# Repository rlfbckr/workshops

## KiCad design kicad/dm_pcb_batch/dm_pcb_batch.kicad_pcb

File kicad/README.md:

# Designing PCBs for artists and designers with KiCAD

This is an introduction to KiCAD spanning two evenings. Together, we will design a basic microcontroller board around an ATtiny microcontroller. The workshop will cover all the steps involved, from creating the schematic and designing the board to preparing it for fabrication.

## Reqiements
- You have a strong grasp of electronics and have already completed several Arduino/microcontroller projects. You are also familiar with reading schematics and understanding Ohm's law.

## Prepare for Workshop
- download KiCAD (version 9) from https://www.kicad.org/

## Additonal Resources
- [Introduction](https://docs.google.com/presentation/d/1FQOJmnPphsIvtIlYlx94JYpmJ64v6YoRFoZGHLRAc9c/edit?slide=id.p#slide=id.p) 
- [6 Horribly Common PCB Design Mistakes](https://www.youtube.com/watch?v=Z9nycymUd-I)
- [PCB Batch Miro Boards](https://miro.com/app/board/uXjVJfeq8kw=/)

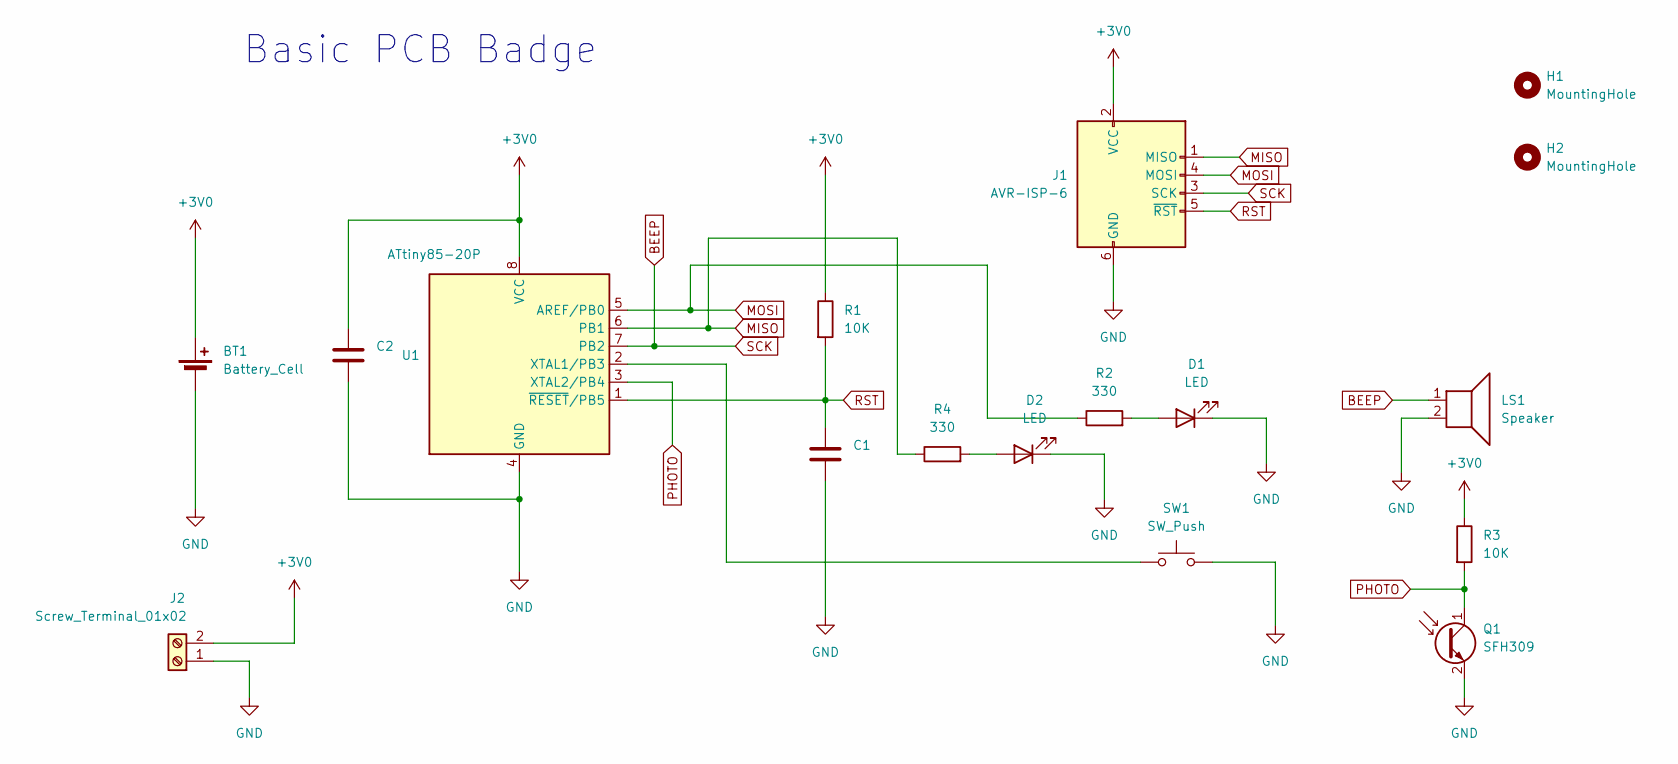
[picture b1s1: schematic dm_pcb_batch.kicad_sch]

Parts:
BT1: Battery_Cell; BatteryHolder_Multicomp_BC-2001_1x2032
C1, C2: 100n; C_Disc_D3.8mm_W2.6mm_P2.50mm
D1, D2: LED; LED_D3.0mm
H1, H2: MountingHole; MountingHole_3.2mm_M3
J1: AVR-ISP-6; PinHeader_2x03_P2.54mm_Vertical
J2: Screw_Terminal_01x02
LS1: Speaker; Buzzer_12x9.5RM7.6
Q1: SFH309; LED_D3.0mm_Clear
R1, R3: 10K; R_Axial_DIN0207_L6.3mm_D2.5mm_P10.16mm_Horizontal
R2, R4: 330; R_Axial_DIN0207_L6.3mm_D2.5mm_P10.16mm_Horizontal
SW1: SW_Push; SW_PUSH_6mm
U1: ATtiny85-20P; DIP-8_W7.62mm

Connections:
+3V0: BT1.1 (+), C2.1, J1.2 (VCC), J2.2, R1.1, R3.1, U1.8 (VCC)
BEEP: J1.3 (SCK), LS1.1, U1.7 (PB2)
GND: BT1.2 (-), C1.2, C2.2, D1.1 (K), D2.1 (K), J1.6 (GND), J2.1, LS1.2, Q1.2 (E), SW1.2, U1.4 (GND)
MISO: J1.1 (MISO), R4.1, U1.6 (PB1)
MOSI: J1.4 (MOSI), R2.1, U1.5 (AREF/PB0)
unnamed: D1.2 (A), R2.2
unnamed: D2.2 (A), R4.2
unnamed: SW1.1, U1.2 (XTAL1/PB3)
PHOTO: Q1.1 (C), R3.2, U1.3 (XTAL2/PB4)
RST: C1.1, J1.5 (~RST), R1.2, U1.1 (~RESET/PB5)

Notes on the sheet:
Basic PCB Badge

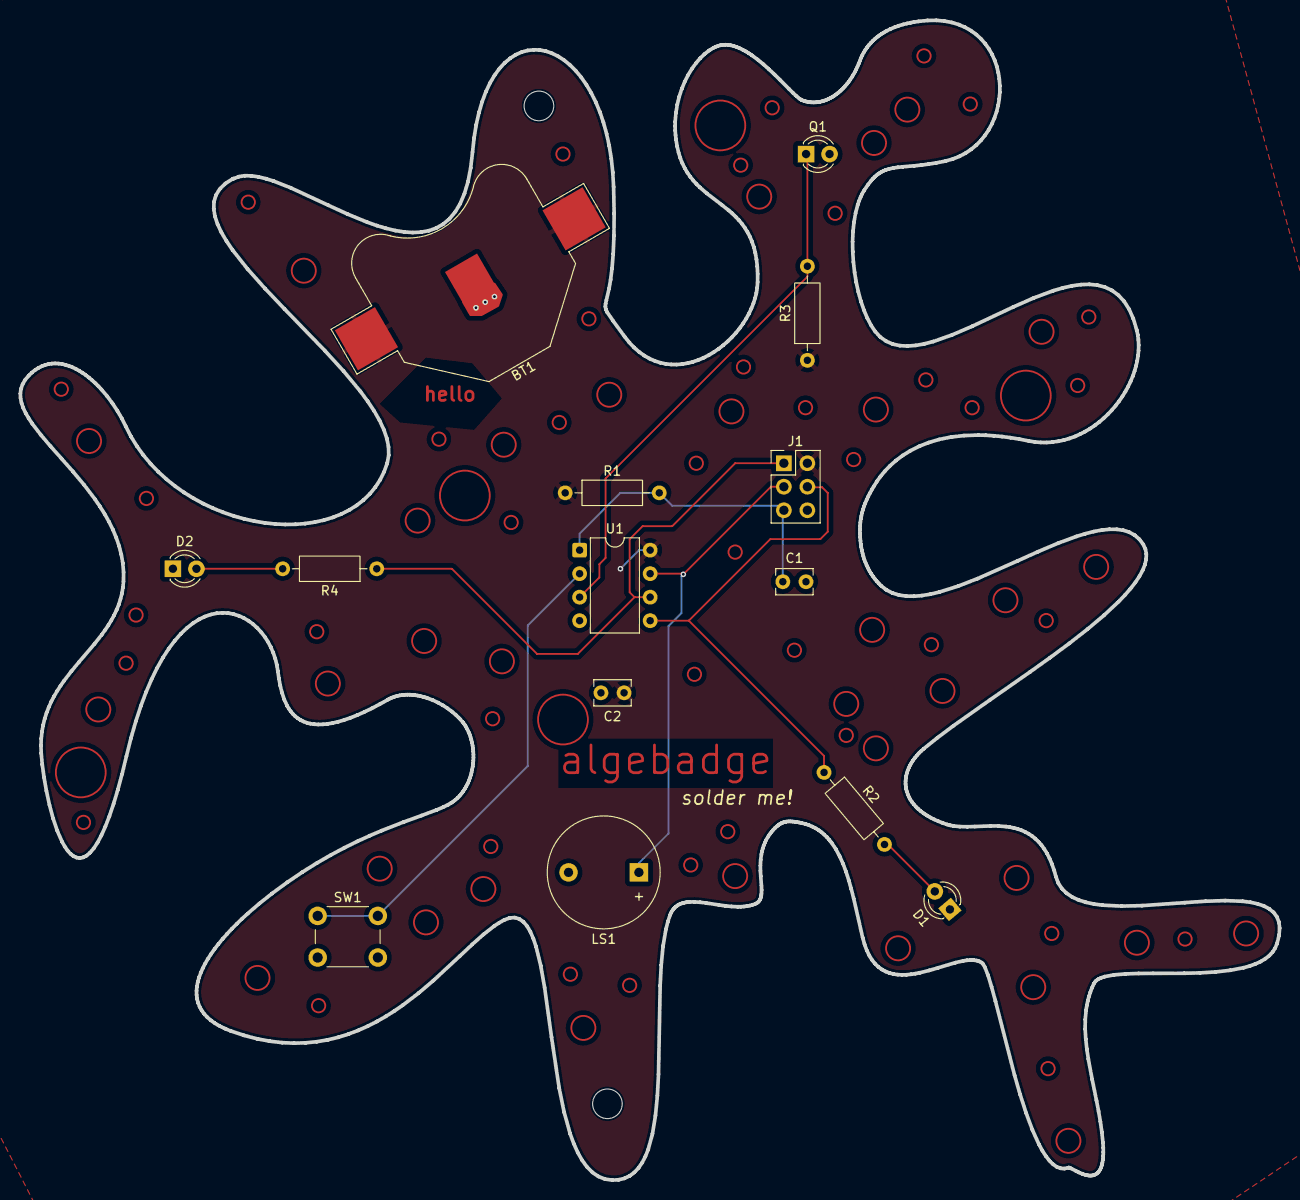
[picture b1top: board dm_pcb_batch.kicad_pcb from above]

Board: 2 copper layers, 136.0 x 125.3 mm, 16 parts (0 on the bottom side), 10 nets.

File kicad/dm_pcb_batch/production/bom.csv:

Designator,Footprint,Quantity,Value,LCSC Part #
BT1,BatteryHolder_Multicomp_BC-2001_1x2032,1,Battery_Cell,
"C1, C2",C_Disc_D3.8mm_W2.6mm_P2.50mm,2,100n,
"D1, D2",LED_D3.0mm,2,LED,
J1,PinHeader_2x03_P2.54mm_Vertical,1,AVR-ISP-6,
LS1,Buzzer_12x9.5RM7.6,1,Speaker,
Q1,LED_D3.0mm_Clear,1,SFH309,
"R1, R3",R_Axial_DIN0207_L6.3mm_D2.5mm_P10.16mm_Horizontal,2,10K,
"R2, R4",R_Axial_DIN0207_L6.3mm_D2.5mm_P10.16mm_Horizontal,2,330,
SW1,SW_PUSH_6mm,1,SW_Push,
U1,DIP-8_W7.62mm,1,ATtiny85-20P,

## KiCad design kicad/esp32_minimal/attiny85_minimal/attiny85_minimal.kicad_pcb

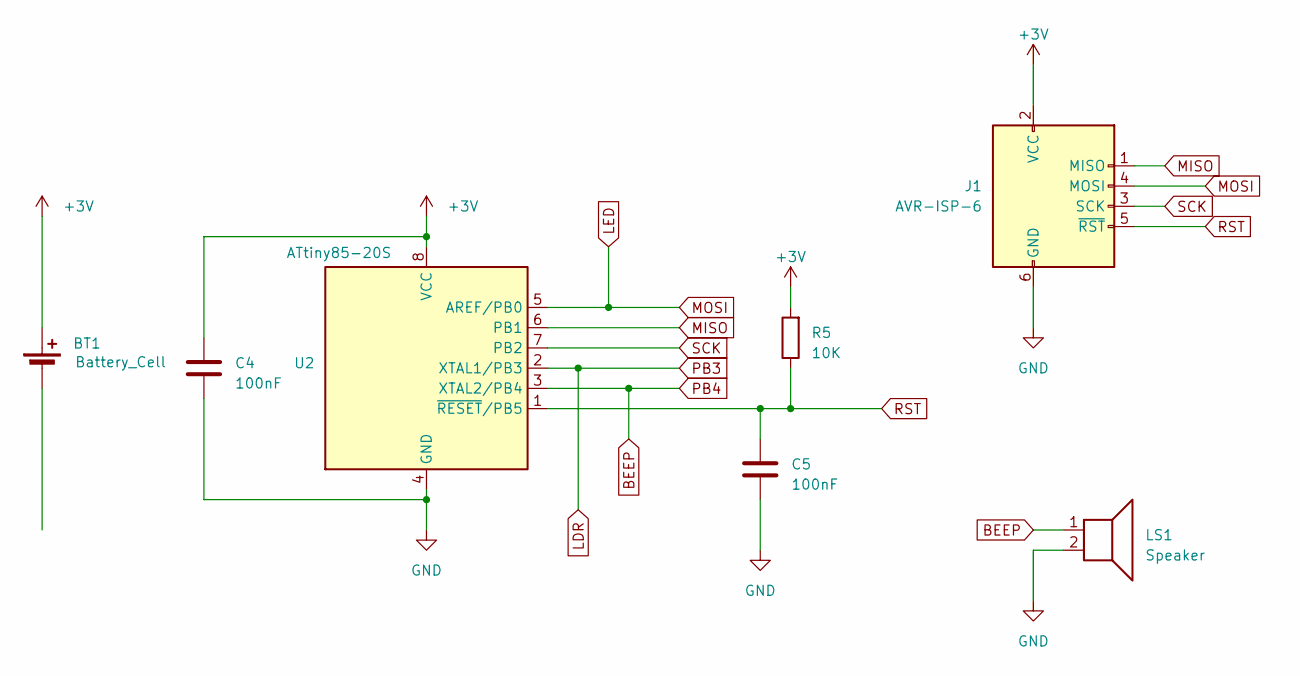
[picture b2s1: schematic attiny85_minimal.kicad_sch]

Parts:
BT1: Battery_Cell; Battery_Panasonic_CR2032-HFN_Horizontal_CircularHoles
C4, C5: 100nF; C_Disc_D5.0mm_W2.5mm_P5.00mm
J1: AVR-ISP-6; PinHeader_2x03_P2.54mm_Vertical
LS1: Speaker; Buzzer_12x9.5RM7.6
R5: 10K; R_Axial_DIN0614_L14.3mm_D5.7mm_P5.08mm_Vertical
U2: ATtiny85-20S; CERDIP-8_W7.62mm_SideBrazed_LongPads_Socket

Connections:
+3V: BT1.1 (+), C4.1, J1.2 (VCC), R5.2, U2.8 (VCC)
BEEP: LS1.1, U2.3 (XTAL2/PB4)
GND: BT1.2 (-), C4.2, C5.2, J1.6 (GND), LS1.2, U2.4 (GND)
MISO: J1.1 (MISO), U2.6 (PB1)
MOSI: J1.4 (MOSI), U2.5 (AREF/PB0)
PB3: U2.2 (XTAL1/PB3)
RST: C5.1, J1.5 (~RST), R5.1, U2.1 (~RESET/PB5)
SCK: J1.3 (SCK), U2.7 (PB2)

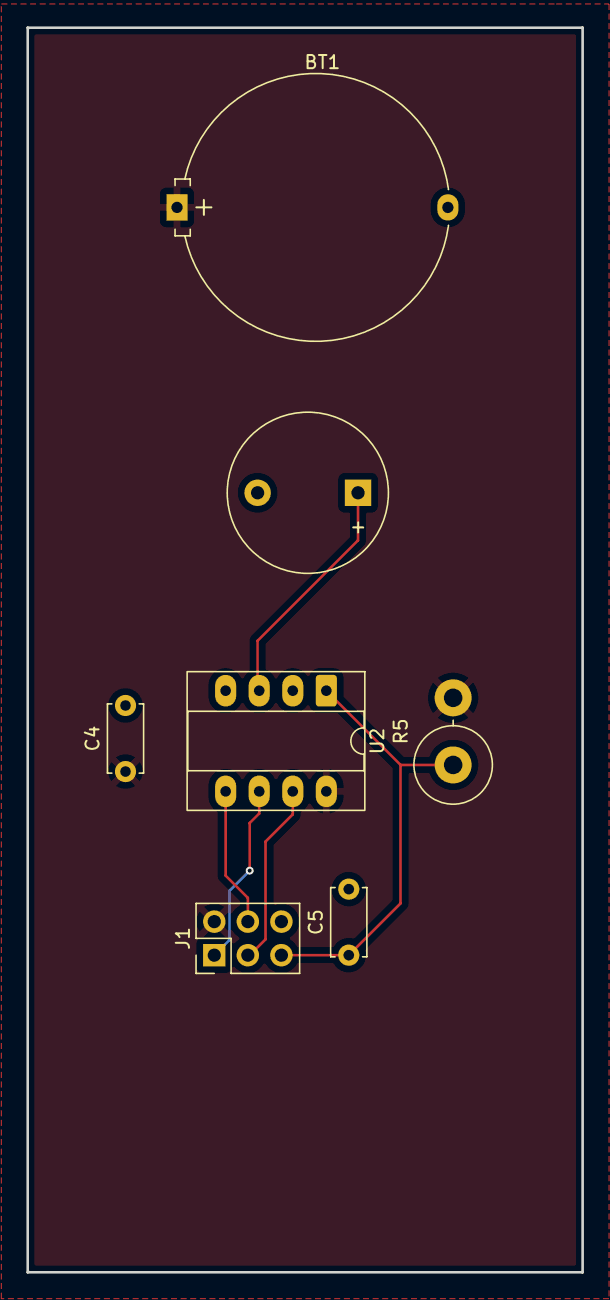
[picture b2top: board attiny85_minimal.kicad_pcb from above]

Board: 2 copper layers, 42.0 x 94.2 mm, 7 parts (0 on the bottom side), 7 nets.

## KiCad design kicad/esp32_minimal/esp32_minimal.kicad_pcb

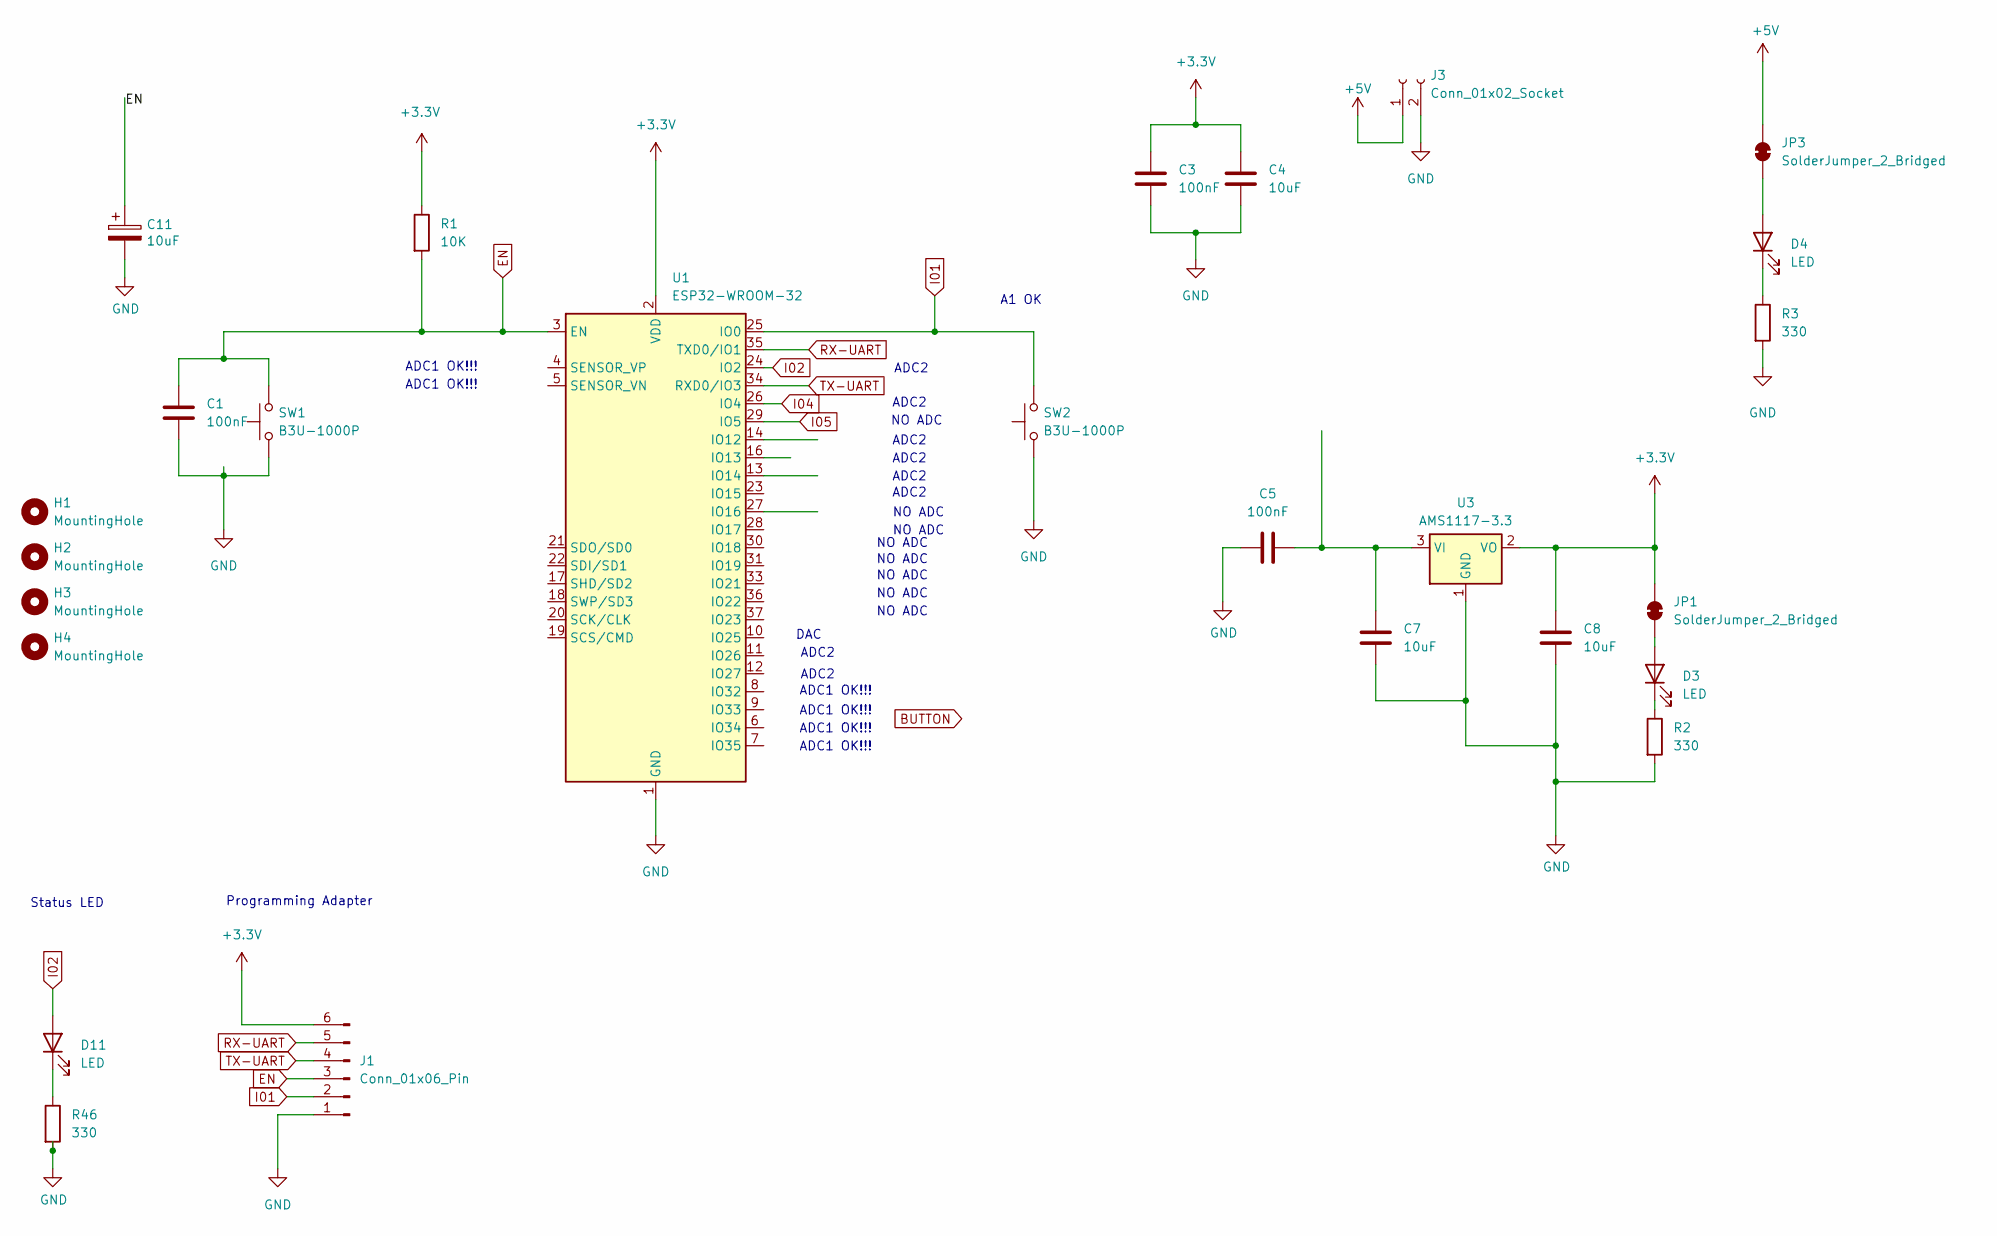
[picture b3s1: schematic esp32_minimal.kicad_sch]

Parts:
C1, C3, C5: 100nF; C_0603_1608Metric
C4, C7, C8: 10uF; C_0603_1608Metric
C11: 10uF; CP_EIA-3216-18_Kemet-A; MPN C7171
D3: LED; LED_0805_2012Metric; MPN C2297
D4: LED; LED_0805_2012Metric
D11: LED; LED_0805_2012Metric; MPN C34499
H1, H2, H3, H4: MountingHole; MountingHole_3.2mm_M3
J1: Conn_01x06_Pin; PinHeader_1x06_P2.54mm_Vertical; JLCPCB Rotation Offset -90
J3: Conn_01x02_Socket; JST_NV_B02P-NV_1x02_P5.00mm_Vertical
JP1, JP3: SolderJumper_2_Bridged; SolderJumper-2_P1.3mm_Open_RoundedPad1.0x1.5mm
R1: 10K; R_0603_1608Metric
R2, R3, R46: 330; R_0603_1608Metric
SW1, SW2: B3U-1000P; SW_SPST_B3U-1000P
U1: ESP32-WROOM-32
U3: AMS1117-3.3; SOT-223-3_TabPin2

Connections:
+3.3V: C3.1, C4.1, C8.2, J1.6, JP1.2 (B), R1.1, U1.2 (VDD), U3.2 (VO)
+5V: J3.1, JP3.2 (B)
EN: C1.1, C11.1, J1.3, R1.2, SW1.2, U1.3 (EN)
GND: C1.2, C3.2, C4.2, C5.1, C7.2, C8.1, C11.2, J1.1, J3.2, R2.2, R3.2, R46.2, SW1.1, SW2.1, U1.1 (GND), U1.15 (GND), U1.38 (GND), U1.39 (GND), U3.1 (GND)
I01: J1.2, SW2.2, U1.25 (IO0)
I02: D11.2 (A), U1.24 (IO2)
I04: U1.26 (IO4)
I05: U1.29 (IO5)
unnamed: D3.2 (A), JP1.1 (A)
unnamed: D3.1 (K), R2.1
unnamed: D4.2 (A), JP3.1 (A)
unnamed: D4.1 (K), R3.1
unnamed: D11.1 (K), R46.1
unnamed: C5.2, C7.1, U3.3 (VI)
RX-UART: J1.5, U1.35 (TXD0/IO1)
TX-UART: J1.4, U1.34 (RXD0/IO3)

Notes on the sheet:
NO ADC
DAC
Status LED
ADC2
ADC1 OK!!!
Programming Adapter
A1 OK

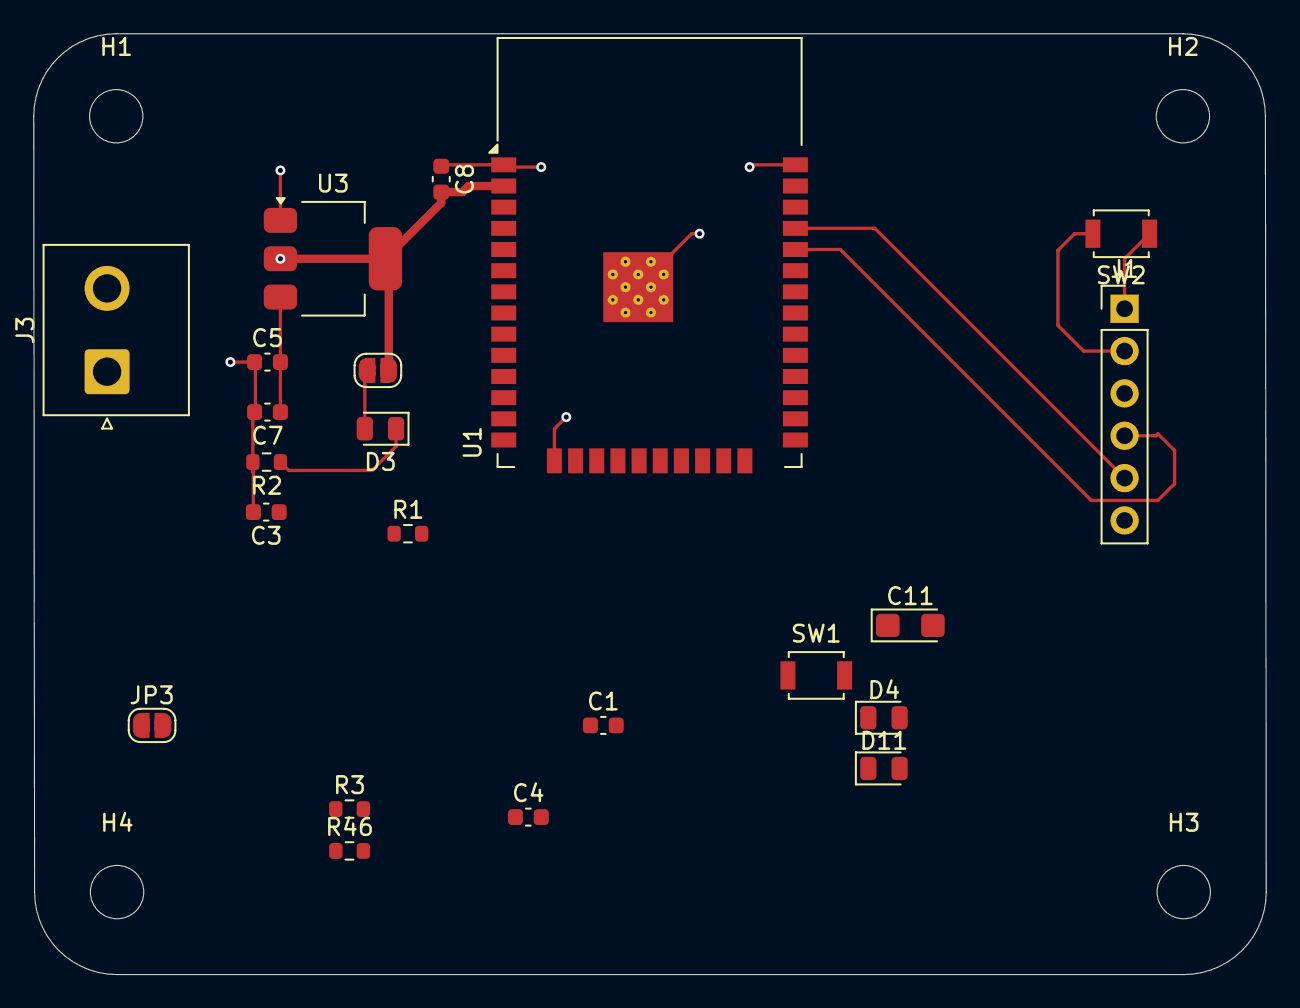
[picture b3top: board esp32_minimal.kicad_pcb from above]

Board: 2 copper layers, 73.9 x 56.4 mm, 26 parts (0 on the bottom side), 14 nets.

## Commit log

2025-07-15 smal fixes ntaa etc
2026-05-20 new menu bar, header fiexed, new mono font etc
